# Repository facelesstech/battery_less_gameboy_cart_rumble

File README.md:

# battery_less_gameboy_cart_rumble
battery_less_gameboy_cart_rumble

* [Blog post](https://facelesstech.wordpress.com/2023/08/26/pokemon-pinball-without-the-battery/)

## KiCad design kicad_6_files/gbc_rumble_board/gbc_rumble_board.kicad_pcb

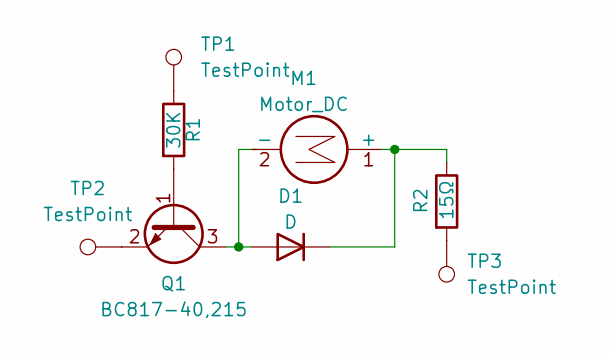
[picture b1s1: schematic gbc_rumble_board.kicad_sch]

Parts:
D1: D; D_SOD-123
M1: Motor_DC; ANDA-T1035_vib_motor
Q1: BC817-40,215; SOT-23
R1: 30K; R_0603_1608Metric
R2: 15Ω; R_0603_1608Metric
TP1, TP2, TP3: TestPoint; 2mm_test_point_smd

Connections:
unnamed: D1.1 (K), M1.1 (+), R2.1
unnamed: D1.2 (A), M1.2 (-), Q1.3 (C)
unnamed: Q1.1 (B), R1.2
unnamed: Q1.2 (E), TP2.1
unnamed: R1.1, TP1.1
unnamed: R2.2, TP3.1

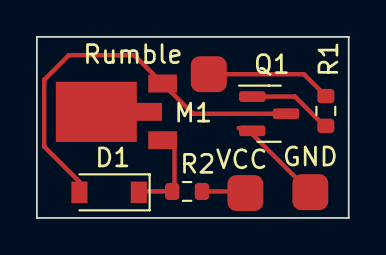
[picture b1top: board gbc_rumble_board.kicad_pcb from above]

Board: 2 copper layers, 17.3 x 10.1 mm, 8 parts (0 on the bottom side), 6 nets.

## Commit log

2023-08-26 added kicad files
2023-08-26 added the 3d printing files
2023-10-14 added photo
2023-10-14 added blog post and photo to readme
